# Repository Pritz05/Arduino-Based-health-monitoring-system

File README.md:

# L1 — Heart Rate & SpO2 Monitor

A compact Arduino Nano-based pulse oximeter and blood oxygen monitor with OLED display and button navigation.

---

## 📦 Components

| Reference | Component | Description |
|-----------|-----------|-------------|
| U_MCU | Arduino Nano v3.x | Main microcontroller |
| U1 | MAX30102_mod | Heart rate & SpO2 sensor (I2C) |
| U2 | SSD1306 | 128x64 OLED display (I2C) |
| SW1, SW2, SW3 | SW_Push | Tactile push buttons |
| C1, C2, C3 | 100nF capacitor | Button debounce capacitors |
| R1, R2, R3 | 1kΩ resistor | Button pull-up resistors |
| R4 | 1kΩ resistor | LED current limiting resistor |
| D1 | LED | Status indicator LED |

---

## 🔌 Pin Connections

| Arduino Pin | Connected To |
|-------------|--------------|
| A4 (SDA) | MAX30102 SDA, SSD1306 SDA |
| A5 (SCL) | MAX30102 SCL, SSD1306 SCL |
| A1 | Analog input (button or sensor) |
| D2–D13 | Available for button/LED assignment |
| +5V | VCC for all modules |
| GND | Common ground |

> **Note:** Both the MAX30102 and SSD1306 share the I2C bus (A4/A5). Their I2C addresses must be different (MAX30102: `0x57`, SSD1306: `0x3C` or `0x3D`).

---

## ⚡ Power

- Powered via USB through the Arduino Nano's onboard regulator
- All peripherals run on **+5V**
- Decoupling capacitors (100nF) on each button line for debounce

---

## 🛠️ Building & Flashing

### Requirements
- [Arduino IDE](https://www.arduino.cc/en/software) or PlatformIO
- Libraries:
  - `MAX3010x` (SparkFun or similar)
  - `Adafruit SSD1306`
  - `Adafruit GFX`

### Steps
1. Clone this repository
2. Open the sketch in Arduino IDE
3. Select **Board:** `Arduino Nano` and the correct **Port**
4. Install required libraries via Library Manager
5. Upload

---

## 📁 Repository Structure

```
├── L1.kicad_pro          # KiCad project file
├── L1.kicad_sch          # Schematic
├── L1.kicad_pcb          # PCB layout
├── L1.kicad_sym          # Custom schematic symbols
├── for_custom.pretty/    # Custom footprints
├── fp-lib-table          # Footprint library table
├── sym-lib-table         # Symbol library table
└── README.md
```

---

## 📐 PCB

Designed in **KiCad 9.0**.

> Gerber files and fabrication outputs can be found in the `/fab` directory (if included).

---

## 📄 License

MIT License — feel free to use, modify, and distribute.

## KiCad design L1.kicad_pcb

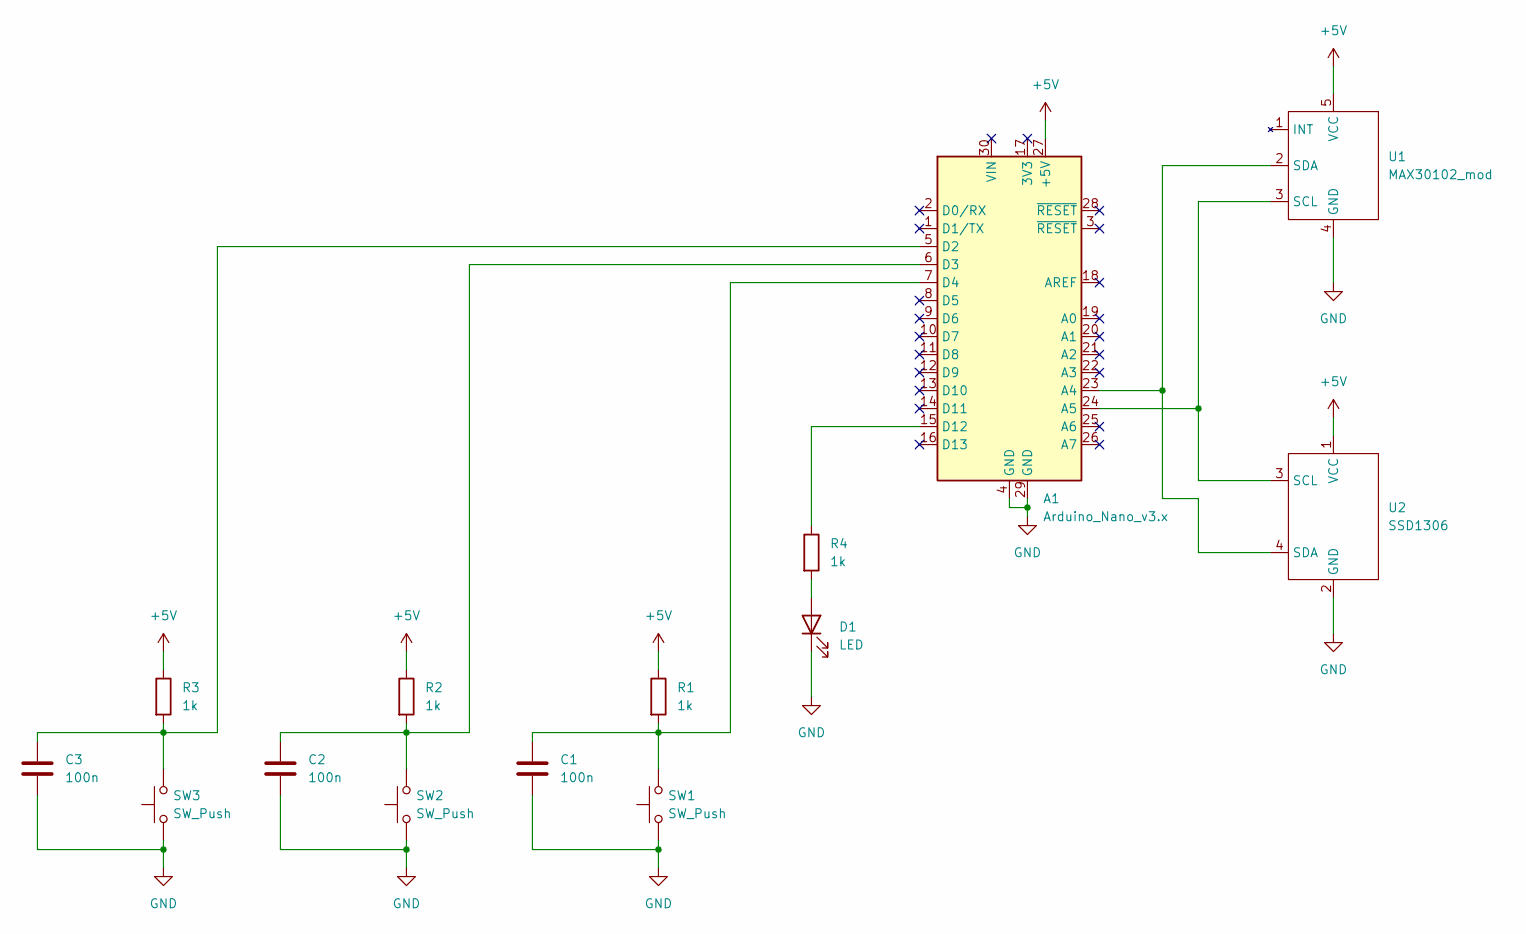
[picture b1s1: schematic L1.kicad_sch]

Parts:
A1: Arduino_Nano_v3.x; Arduino_Nano
C1, C2, C3: 100n; C_Disc_D4.3mm_W1.9mm_P5.00mm
D1: LED; LED_D5.0mm
R1, R2, R3, R4: 1k; R_Axial_DIN0207_L6.3mm_D2.5mm_P7.62mm_Horizontal
SW1, SW2, SW3: SW_Push; SW_PUSH_6mm
U1: MAX30102_mod
U2: SSD1306

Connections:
+5V: A1.27 (+5V), R1.1, R2.1, R3.1, U1.5 (VCC), U2.1 (VCC)
GND: A1.4 (GND), A1.29 (GND), C1.2, C2.2, C3.2, D1.1 (K), SW1.1, SW2.1, SW3.1, U1.4 (GND), U2.2 (GND)
unnamed: A1.23 (A4), U1.2 (SDA), U2.4 (SDA)
unnamed: A1.24 (A5), U1.3 (SCL), U2.3 (SCL)
unnamed: A1.5 (D2), C3.1, R3.2, SW3.2
unnamed: A1.6 (D3), C2.1, R2.2, SW2.2
unnamed: A1.7 (D4), C1.1, R1.2, SW1.2
unnamed: A1.15 (D12), R4.1
unnamed: D1.2 (A), R4.2

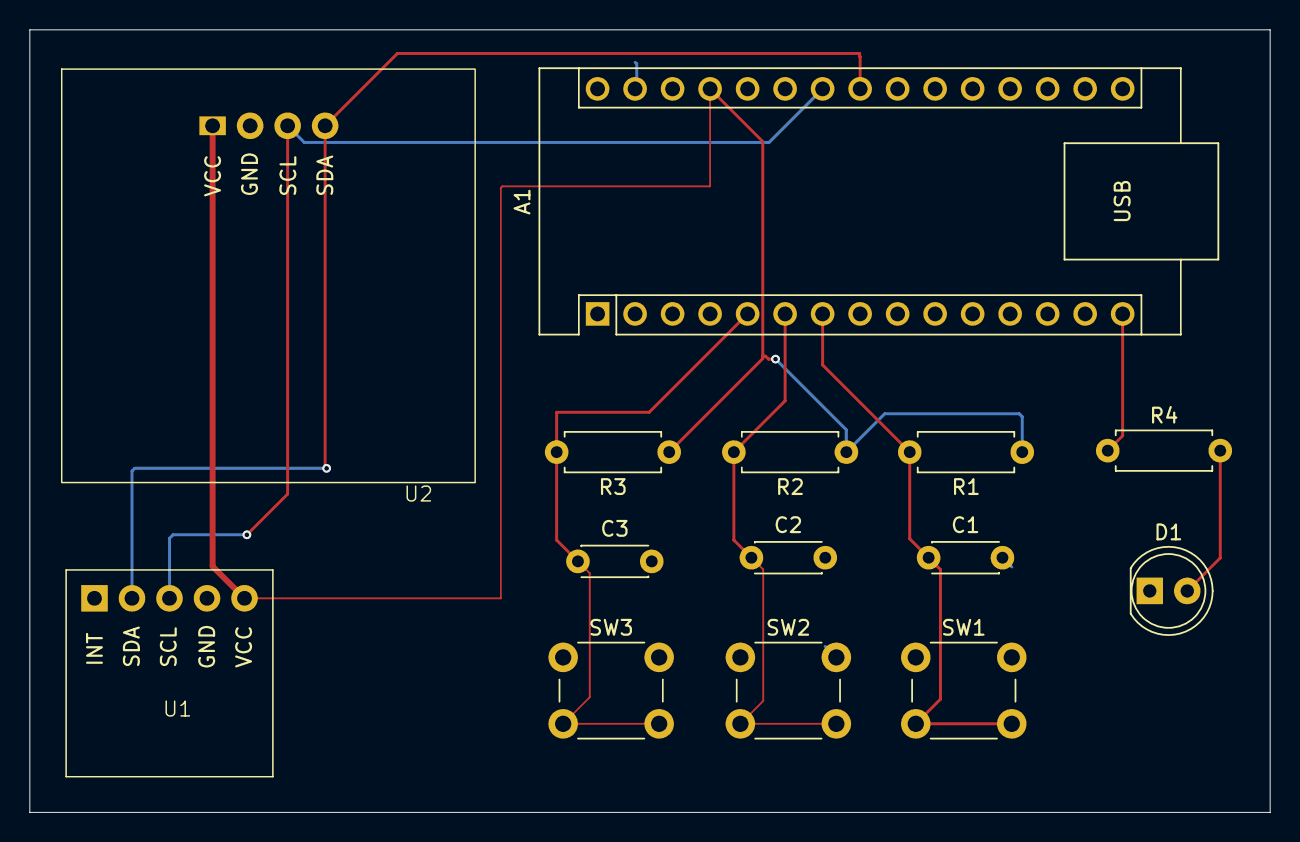
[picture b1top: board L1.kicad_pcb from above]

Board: 4 copper layers, 84.0 x 53.0 mm, 14 parts (0 on the bottom side), 9 nets.
